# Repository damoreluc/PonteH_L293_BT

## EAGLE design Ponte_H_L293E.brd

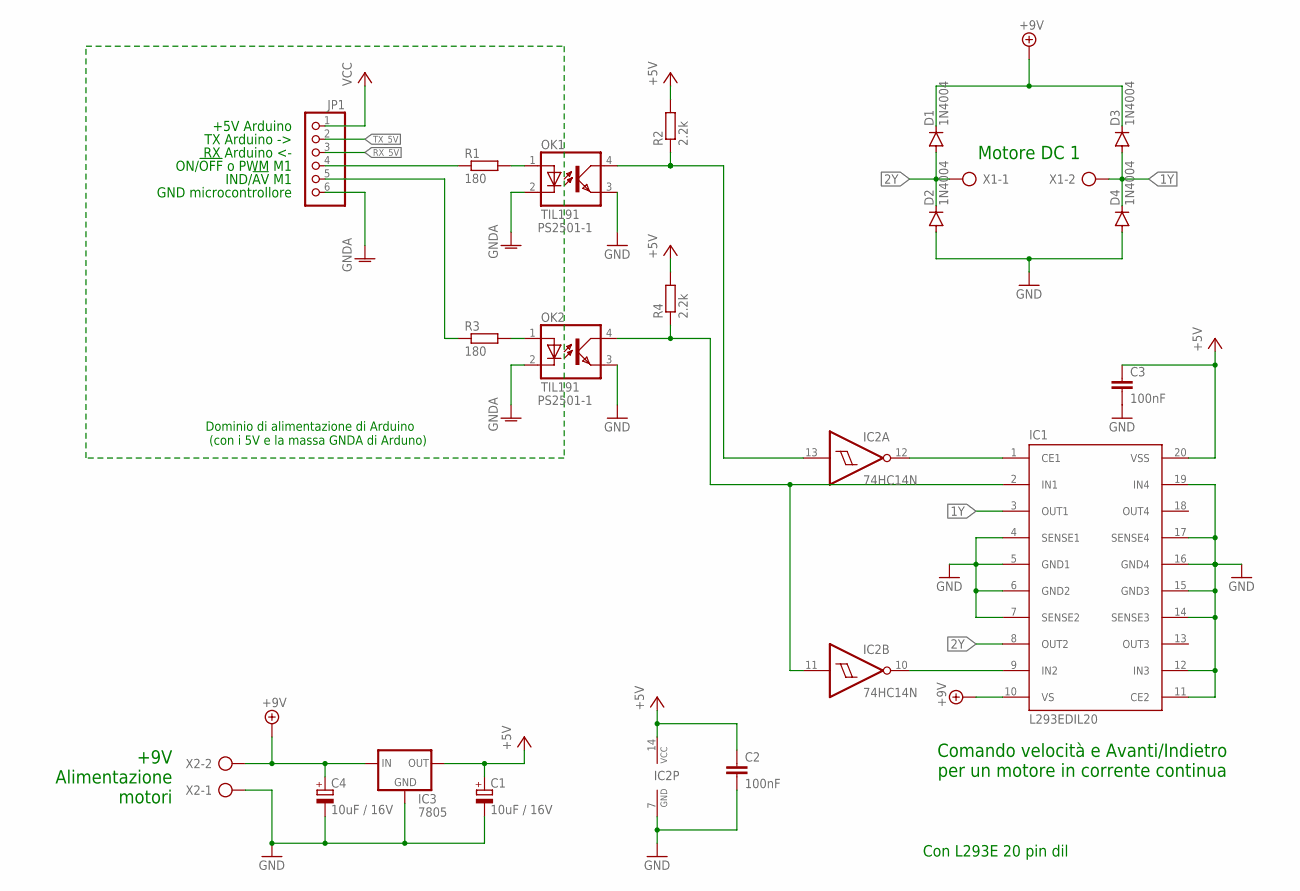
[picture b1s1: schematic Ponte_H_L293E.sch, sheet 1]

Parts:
C1, C4: 10uF / 16V; E5-8,5
C2, C3: 100nF; C050-025X075
D1, D2, D3, D4: 1N4004; DO41-10
IC1: L293EDIL20; DIL20
IC2: 74HC14N; DIL14
IC3: 7805; 78XXS
JP1: PINHD-1X6; 1X06
OK1, OK2: TIL191; DIL04
R1, R3: 180; 0207/10
R2, R4: 2.2k; 0207/10
X1, X2: AK500/2

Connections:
1Y: D3.A, D4.C, IC1.3 (OUT1), X1.2
2Y: D1.A, D2.C, IC1.8 (OUT2), X1.1
+5V: C1.+, C2.1, C3.1, IC1.20 (VSS), IC2.14 (VCC), IC3.OUT, R2.2, R4.2
+9V: C4.+, D1.C, D3.C, IC1.10 (VS), IC3.IN, X2.2
GND: C1.-, C2.2, C3.2, C4.-, D2.A, D4.A, IC1.4 (SENSE1), IC1.5 (GND1), IC1.6 (GND2), IC1.7 (SENSE2), IC1.11 (CE2), IC1.12 (IN3), IC1.14 (SENSE3), IC1.15 (GND3), IC1.16 (GND4), IC1.17 (SENSE4), IC1.19 (IN4), IC2.7 (GND), IC3.GND, OK1.3 (EMIT), OK2.3 (EMIT), X2.1
GNDA: JP1.6, OK1.2 (C), OK2.2 (C); also elsewhere on the board
I/!A!: JP1.5, R3.1
unnamed: IC1.1 (CE1), IC2.12 (O)
unnamed: IC1.2 (IN1), IC2.11 (I), OK2.4 (COL), R4.1
unnamed: OK2.1 (A), R3.2
unnamed: IC1.9 (IN2), IC2.10 (O)
unnamed: OK1.1 (A), R1.2
unnamed: IC2.13 (I), OK1.4 (COL), R2.1
PWM: JP1.4, R1.1
RX_5V: JP1.3; also elsewhere on the board
TX_5V: JP1.2; also elsewhere on the board
VCC: JP1.1; also elsewhere on the board

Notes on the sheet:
Con L293E 20 pin dil
Comando velocità e Avanti/Indietro per un motore in corrente continua
ON/!OFF! o PWM M1
IND/!AV! M1
+9V Alimentazione motori
GND microcontrollore
Motore DC 1
Dominio di alimentazione di Arduino (con i 5V e la massa GNDA di Arduno)
TX Arduino ->
RX Arduino <-
+5V Arduino

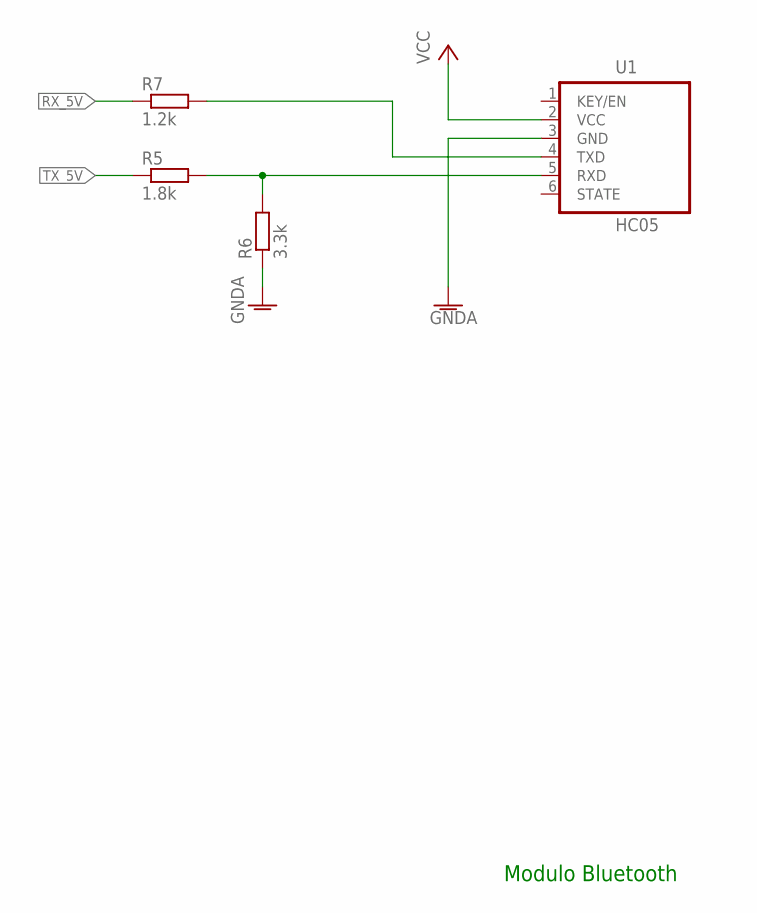
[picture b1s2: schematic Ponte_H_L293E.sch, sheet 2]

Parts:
R5: 1.8k; 0207/10
R6: 3.3k; 0207/10
R7: 1.2k; 0207/10
U1: HC05; HC05-PIN

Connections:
GNDA: R6.1, U1.3 (GND); also elsewhere on the board
unnamed: R7.2, U1.4 (TXD)
unnamed: R5.2, R6.2, U1.5 (RXD)
RX_5V: R7.1; also elsewhere on the board
TX_5V: R5.1; also elsewhere on the board
VCC: U1.2 (VCC); also elsewhere on the board

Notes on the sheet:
Modulo Bluetooth

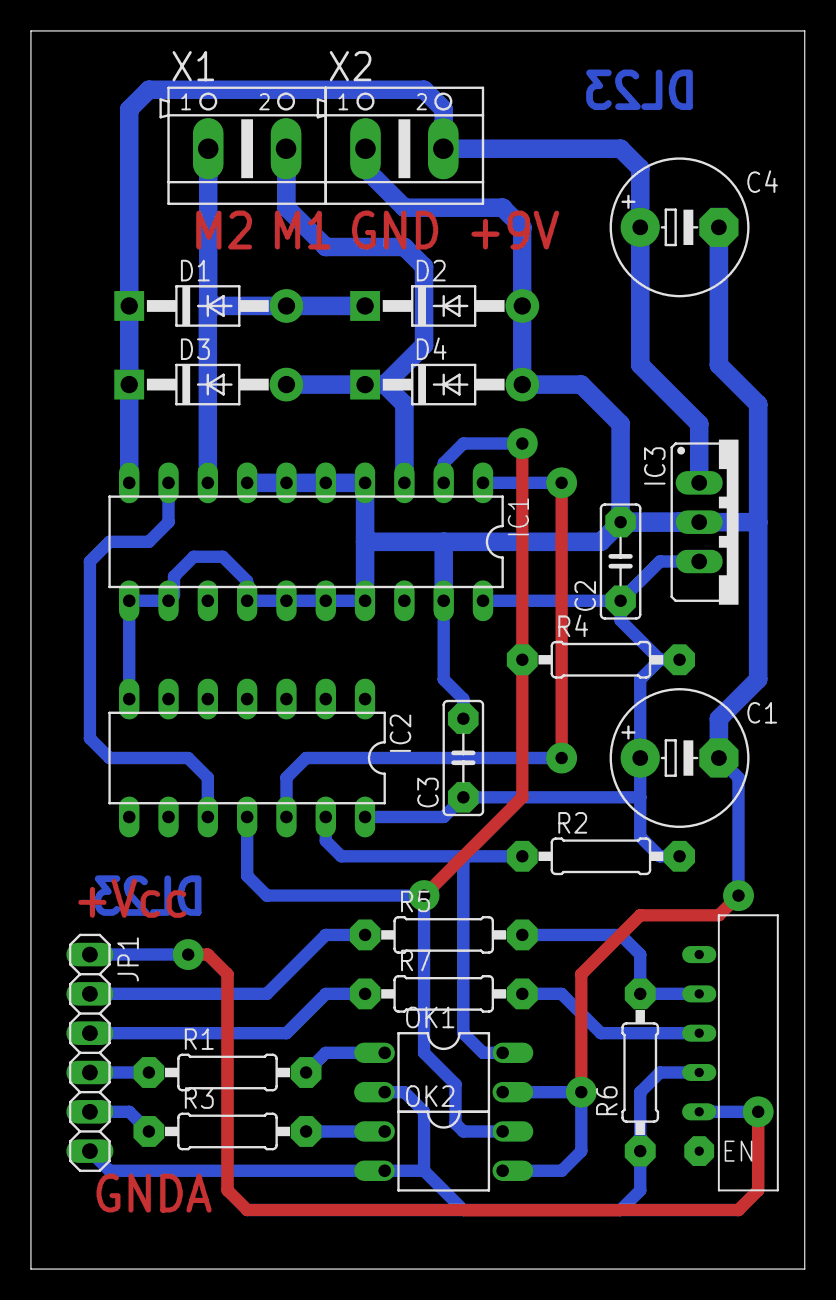
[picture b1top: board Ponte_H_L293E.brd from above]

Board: 2 copper layers, 50.0 x 80.0 mm, 24 parts (0 on the bottom side), 19 nets.

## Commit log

2023-03-12 base vuoto
2023-03-12 schematico L293E+BT
2023-03-12 con PCB
2023-03-13 creato pdf schematico
